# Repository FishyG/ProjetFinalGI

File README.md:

# ProjetFinalGI
Git pour le projet final en GI. Contient l'activité 1 et 3 

https://www.digikey.ca/en/products/detail/sparkfun-electronics/COM-16347/11630204 ws2812b del rgb programmable

Couleurs HTML DELs
https://www.w3schools.com/colors/colors_names.asp

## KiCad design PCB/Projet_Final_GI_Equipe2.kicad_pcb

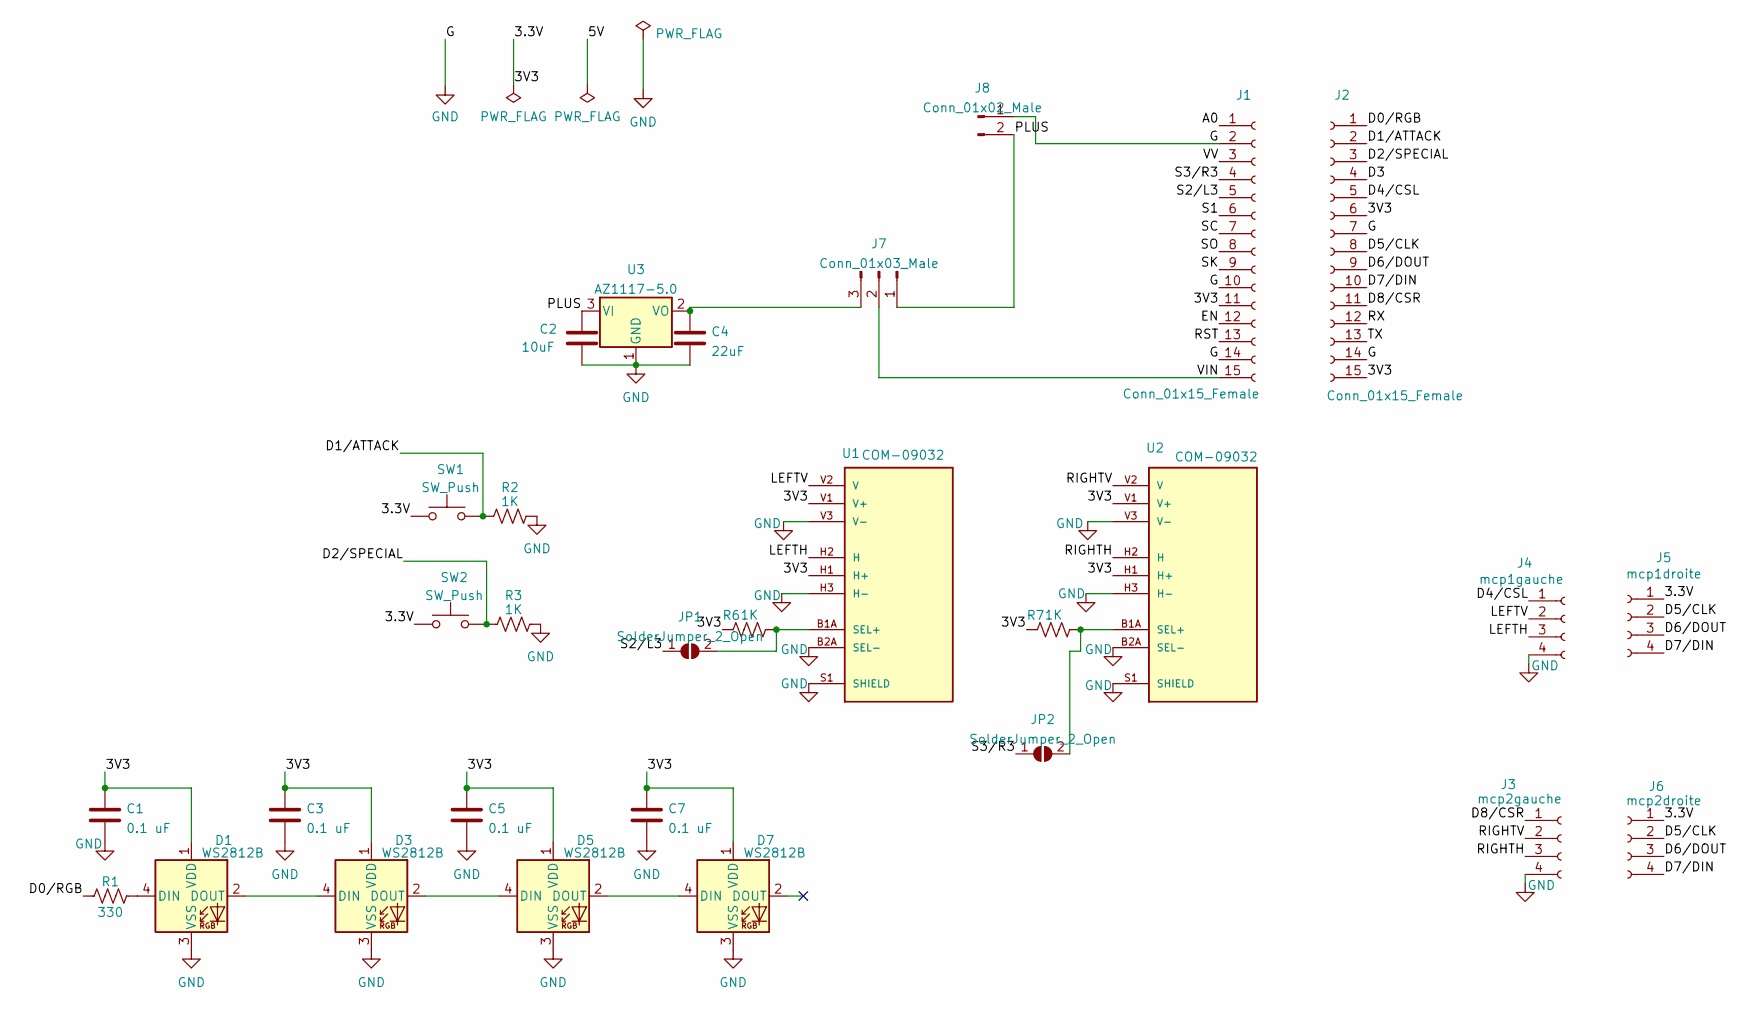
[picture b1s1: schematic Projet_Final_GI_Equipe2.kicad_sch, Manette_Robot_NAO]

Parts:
C1, C3, C5, C7: 0.1 uF; C_0805_2012Metric_Pad1.18x1.45mm_HandSolder
C2: 10uF; C_0805_2012Metric_Pad1.18x1.45mm_HandSolder
C4: 22uF; C_0805_2012Metric_Pad1.18x1.45mm_HandSolder
D1, D3, D5, D7: WS2812B; LED_WS2812B_PLCC4_5.0x5.0mm_P3.2mm
J1, J2: Conn_01x15_Female; PinSocket_1x15_P2.54mm_Vertical
J3: mcp2gauche; PinSocket_1x04_P2.54mm_Vertical
J4: mcp1gauche; PinSocket_1x04_P2.54mm_Vertical
J5: mcp1droite; PinSocket_1x04_P2.54mm_Vertical
J6: mcp2droite; PinSocket_1x04_P2.54mm_Vertical
J7: Conn_01x03_Male; PinHeader_1x03_P2.54mm_Vertical
J8: Conn_01x02_Male; PinHeader_1x02_P2.54mm_Vertical
JP1, JP2: SolderJumper_2_Open; SolderJumper-2_P1.3mm_Open_RoundedPad1.0x1.5mm
R1: 330; C_0805_2012Metric_Pad1.18x1.45mm_HandSolder
R2, R3, R6, R7: 1K; C_0805_2012Metric_Pad1.18x1.45mm_HandSolder
SW1, SW2: SW_Push; SW_PUSH-12mm
U1, U2: COM-09032; XDCR_COM-09032; PARTREV N/A
U3: AZ1117-5.0; SOT-223

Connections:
/3.3V: C1.2, C3.2, C5.2, C7.2, D1.1 (VDD), D3.1 (VDD), D5.1 (VDD), D7.1 (VDD), J1.11, J2.6, J2.15, J5.1, J6.1, R6.1, R7.1, SW1.1, SW2.1, U1.H1 (H+), U1.V1 (V+), U2.H1 (H+), U2.V1 (V+)
/A0: J1.1
/D0/RGB: J2.1, R1.1
/D1/ATTACK: J2.2, R2.1, SW1.2
/D2/SPECIAL: J2.3, R3.1, SW2.2
/D3: J2.4
/D4/CSL: J2.5, J4.1
/D5/CLK: J2.8, J5.2, J6.2
/D6/DOUT: J2.9, J5.3, J6.3
/D7/DIN: J2.10, J5.4, J6.4
/D8/CSR: J2.11, J3.1
/EN: J1.12
/LEFTH: J4.3, U1.H2 (H)
/LEFTV: J4.2, U1.V2 (V)
/PLUS: C2.2, J7.1, J8.2, U3.3 (VI)
/RIGHTH: J3.3, U2.H2 (H)
/RIGHTV: J3.2, U2.V2 (V)
/RST: J1.13
/RX: J2.12
/S1: J1.6
/S2/L3: J1.5, JP1.1 (A)
/S3/R3: J1.4, JP2.1 (A)
/SC: J1.7
/SK: J1.9
/SO: J1.8
/TX: J2.13
/VIN: J1.15, J7.2
/VV: J1.3
GND: C1.1, C2.1, C3.1, C4.1, C5.1, C7.1, D1.3 (VSS), D3.3 (VSS), D5.3 (VSS), D7.3 (VSS), J1.2, J1.10, J1.14, J2.7, J2.14, J3.4, J4.4, J8.1, R2.2, R3.2, U1.B2A (SEL-), U1.H3 (H-), U1.S1 (SHIELD), U1.S2 (SHIELD), U1.S3 (SHIELD), U1.S4 (SHIELD), U1.V3 (V-), U2.B2A (SEL-), U2.H3 (H-), U2.S1 (SHIELD), U2.S2 (SHIELD), U2.S3 (SHIELD), U2.S4 (SHIELD), U2.V3 (V-), U3.1 (GND)
unnamed: C4.2, J7.3, U3.2 (VO)
unnamed: D1.2 (DOUT), D3.4 (DIN)
unnamed: D1.4 (DIN), R1.2
unnamed: D3.2 (DOUT), D5.4 (DIN)
unnamed: D5.2 (DOUT), D7.4 (DIN)
unnamed: JP1.2 (B), R6.2, U1.B1A (SEL+)
unnamed: JP2.2 (B), R7.2, U2.B1A (SEL+)

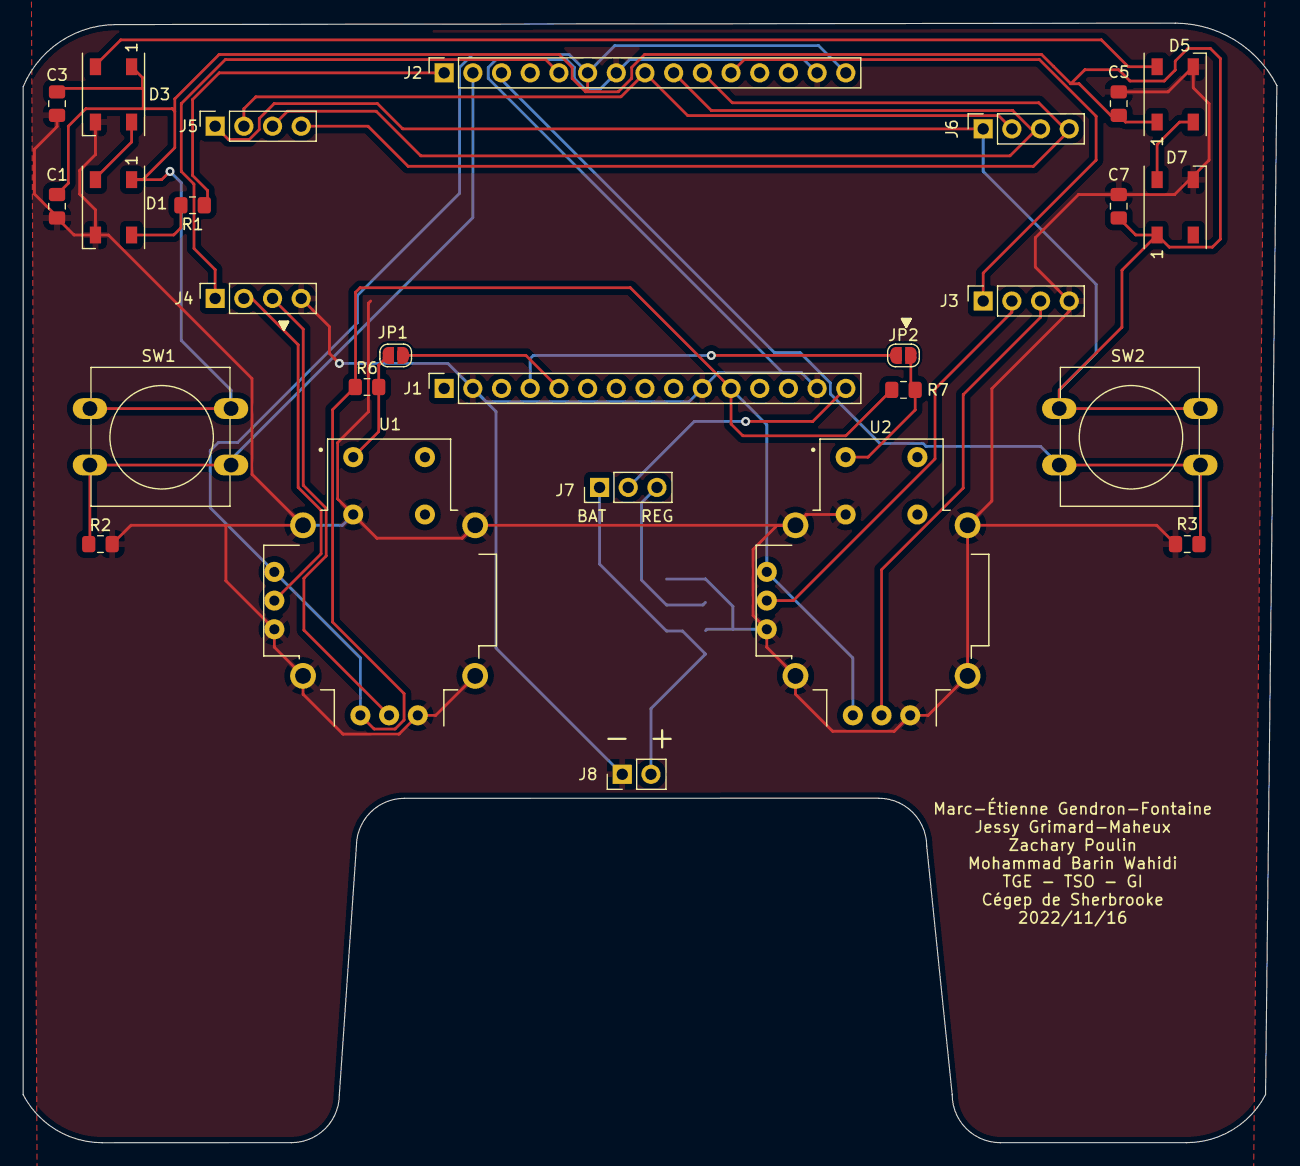
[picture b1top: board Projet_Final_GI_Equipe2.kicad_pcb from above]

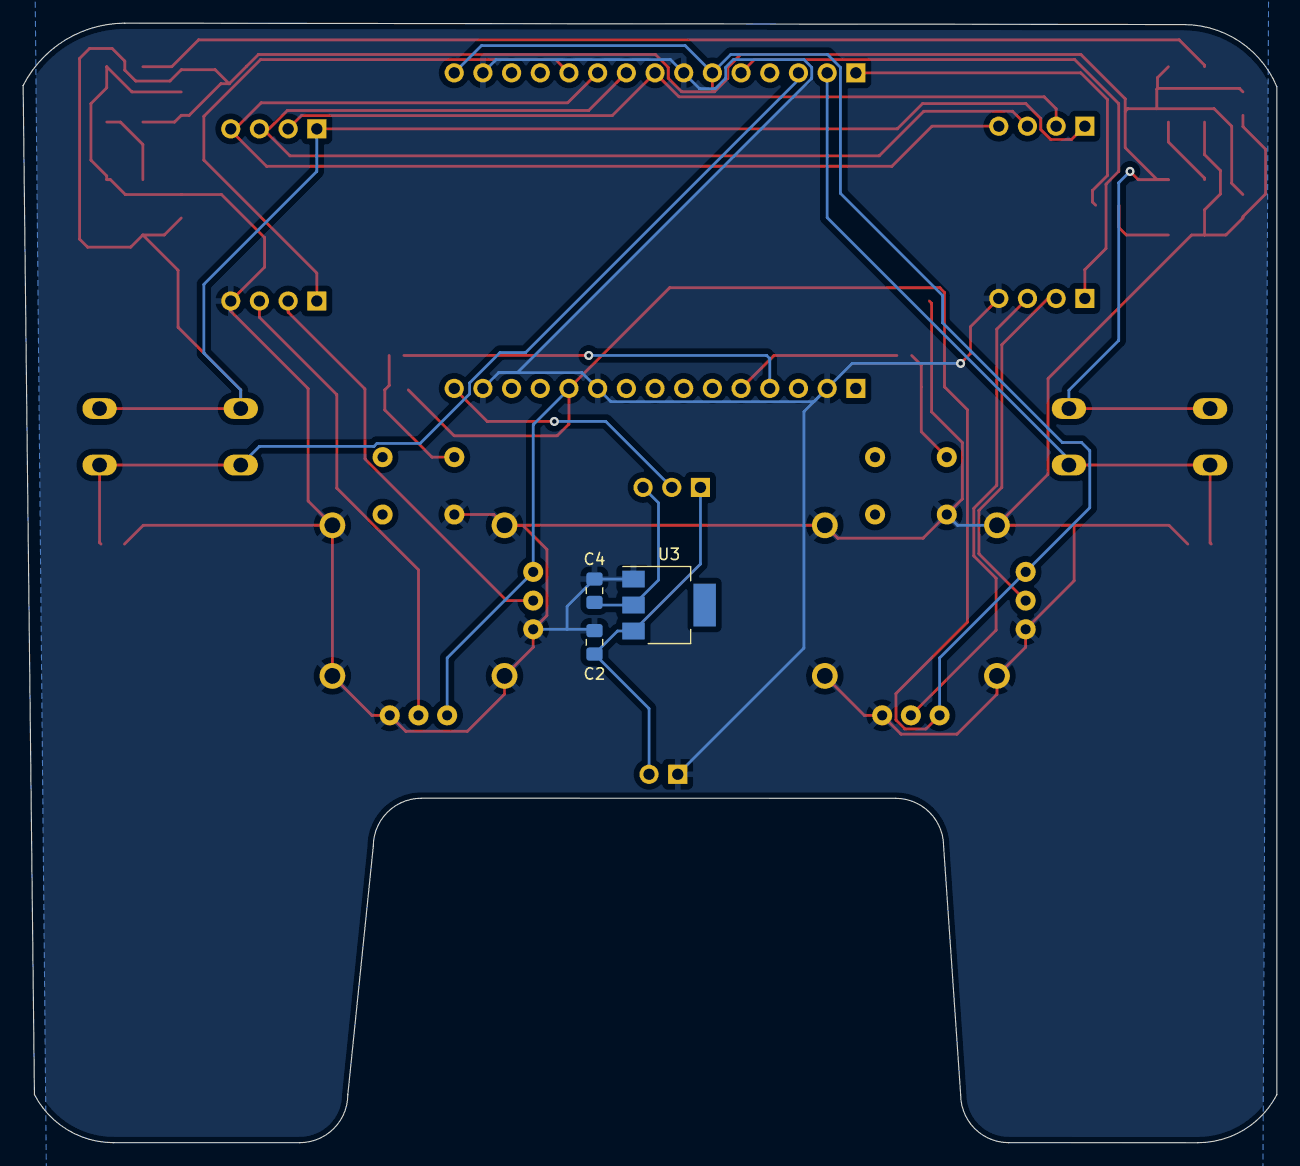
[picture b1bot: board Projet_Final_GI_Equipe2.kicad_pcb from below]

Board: 2 copper layers, 111.0 x 99.1 mm, 30 parts (3 on the bottom side), 25 nets.

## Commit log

2022-11-04 Sailor Moon
2022-11-04 Bruh
2022-11-08 Added the datasheet for MCP3202
2022-11-08 PCBBOZO
2022-11-08 Modif PCB
2022-11-08 Add LED Datasheet
2022-11-09 Cleaned up Readme
2022-11-09 Added Arduino code
2022-11-14 Schema 2.0
2022-11-15 Added mqtt (still broken)
2022-11-15 Jessy doit finir le PCB
2022-11-16 bozoAdd
2022-11-16 J'ai arrondi deux coins en bas
2022-11-16 DEBIANROUILLE TOI
2022-11-16 Robot Nao can now move side to side and backward
2022-11-16 tu peux envoyer tes points, Jessy
2022-11-22 DOC et CODE
2022-11-22 Document pour les bozos de sec1 en format Word
2022-11-22 Ajout du doc Word pour sec 3
2022-11-23 Code Lumiere
2022-11-23 FLASH
2022-11-23 SALUT!!!!
2022-11-23 barin
2022-11-23 Fusion Marc-Étienne/Barin
2022-11-29 Le Code de Jessy
2022-11-29 Ajout du site pour les couleurs dans le Read me
2022-11-29 Création du .h
2022-11-30 New Code (robot NAO can now walk normally)
2022-12-06 Fix Marc-Étienne nuke on my code xD + added debug option
2022-12-06 I wanna sleep x_x
2022-12-06 PCB fix
2022-12-06 suite doc sec 3
2022-12-07 memes
2022-12-07 Remove interrupt dans le projet a jessy
2022-12-07 Added new functions (Barin make good pcb xD)
2022-12-07 modifier le code par les étudiants
2022-12-07 Remove des fichiers odt
2022-12-07 Nuked Backup (Zach = bozo)
2022-12-07 J'attends que Jessy choisisse ses fonctions NAO
2022-12-07 Final version
2022-12-07 Added comment for the schoolboys ang schoolgirls in DEL.ino
2022-12-07 Removed useless prototypes
2022-12-07 Corriger les fautes de Jessy
2022-12-07 ajout section fonctions nao dans doc sec 3
2022-12-07 suicide avant la présentation
2022-12-07 un peu de modif jsp
2022-12-08 flèches rouge à bleu doc sec 1
2022-12-08 Version final PCB Zachary
2022-12-08 J'ai enlevé les memes du doc sec 3
2022-12-08 memes.pdf v2
    J'ai déplacé les memes de la documentation dans le pdf de memes. J'ai rajouté un meme bonus de bleach trouvé sur le net.
2022-12-12 J'ai commenté la majorité de DEL.ino (pour Jessy)
    sauf le code obscur de Marc-Étienne
2022-12-12 Oops. I forgot to put brief
2022-12-13 Documentation finale (Jessy, envoie)
2022-12-13 charniere COMMENTER. Jessy doit COMMENTÉ flash
2022-12-13 j'ai commenté flash
2022-12-16 Final code, comment and all the rest is done
2023-05-10 Create LICENSE
